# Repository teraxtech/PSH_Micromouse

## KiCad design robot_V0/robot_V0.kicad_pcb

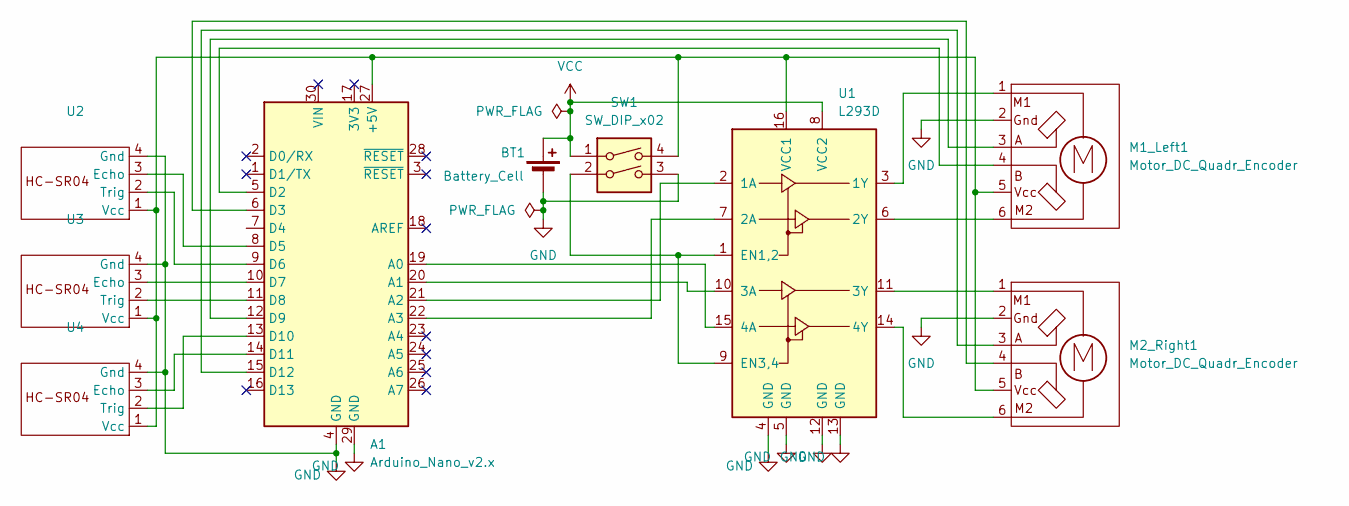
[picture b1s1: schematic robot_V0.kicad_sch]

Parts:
A1: Arduino_Nano_v2.x; Arduino_Nano
BT1: Battery_Cell; PinHeader_1x02_P2.54mm_Vertical
M1_Left1, M2_Right1: Motor_DC_Quadr_Encoder; Molex_CLIK-Mate_505405-0670_1x06-1MP_P1.50mm_Vertical
SW1: SW_DIP_x02; SW_DIP_SPSTx02_Piano_10.8x6.64mm_W7.62mm_P2.54mm
U1: L293D; DIP-16_W7.62mm
U2, U3, U4: XCVR_HC-SR04

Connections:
GND: A1.4 (GND), A1.29 (GND), BT1.2 (-), M1_Left1.2, M2_Right1.2, SW1.3, U1.4 (GND), U1.5 (GND), U1.12 (GND), U1.13 (GND), U2.4 (Gnd), U3.4 (Gnd), U4.4 (Gnd)
unnamed: A1.27 (+5V), M1_Left1.5, M2_Right1.5, SW1.4, U1.16 (VCC1), U2.1 (Vcc), U3.1 (Vcc), U4.1 (Vcc)
unnamed: A1.19 (A0), U1.15 (4A)
unnamed: A1.20 (A1), U1.10 (3A)
unnamed: A1.21 (A2), U1.2 (1A)
unnamed: A1.22 (A3), U1.7 (2A)
unnamed: A1.5 (D2), M1_Left1.4
unnamed: A1.6 (D3), M2_Right1.4
unnamed: A1.8 (D5), U2.3 (Echo)
unnamed: A1.9 (D6), U2.2 (Trig)
unnamed: A1.10 (D7), U3.3 (Echo)
unnamed: A1.11 (D8), U3.2 (Trig)
unnamed: A1.12 (D9), M1_Left1.3
unnamed: A1.13 (D10), U4.2 (Trig)
unnamed: A1.14 (D11), U4.3 (Echo)
unnamed: A1.15 (D12), M2_Right1.3
unnamed: M1_Left1.1, U1.3 (1Y)
unnamed: M1_Left1.6, U1.6 (2Y)
unnamed: M2_Right1.1, U1.11 (3Y)
unnamed: M2_Right1.6, U1.14 (4Y)
unnamed: SW1.2, U1.1 (EN1,2), U1.9 (EN3,4)
VCC: BT1.1 (+), SW1.1, U1.8 (VCC2)

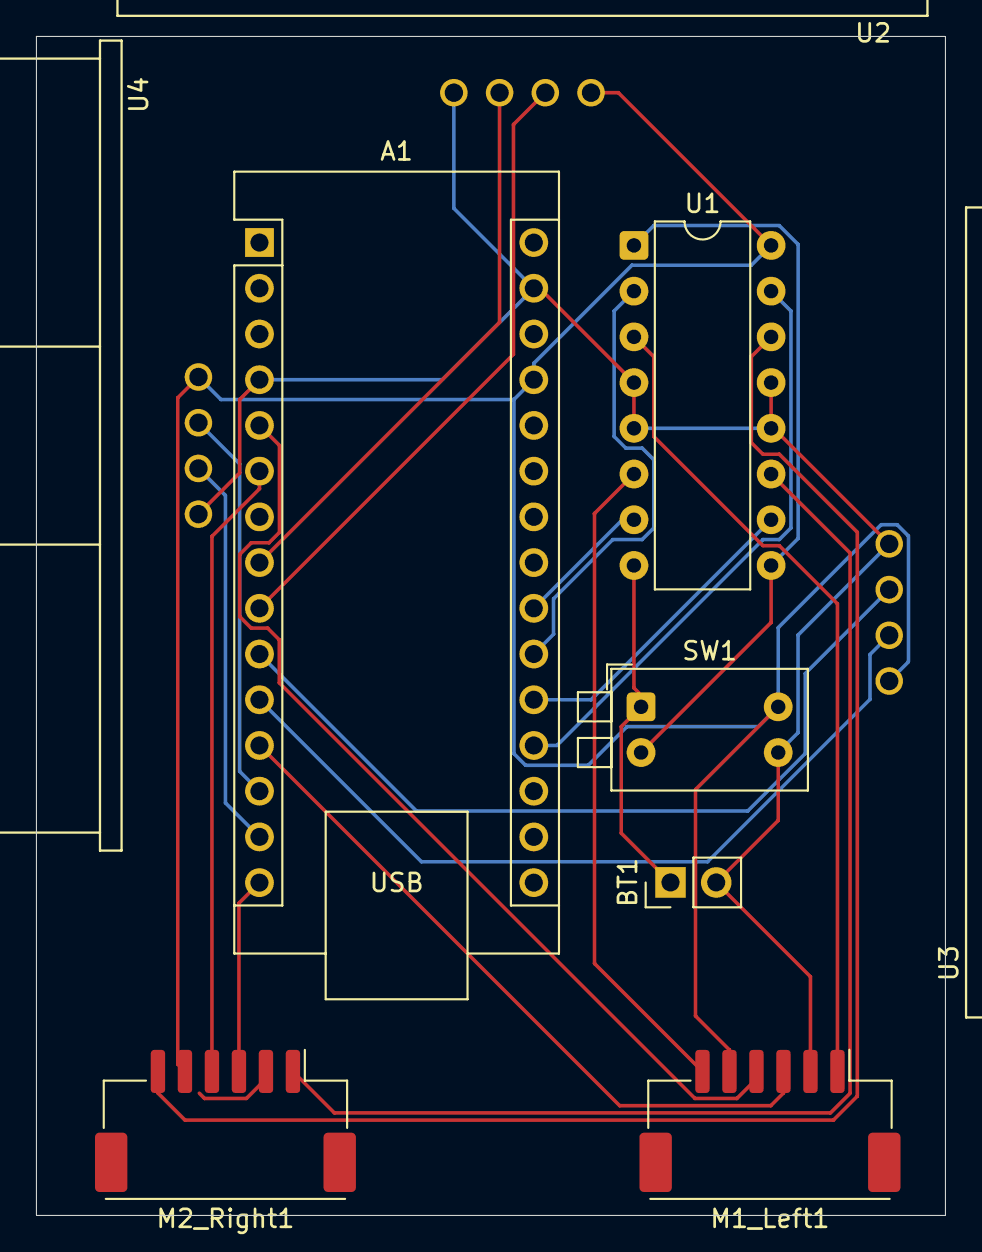
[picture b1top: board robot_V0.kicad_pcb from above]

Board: 2 copper layers, 50.5 x 65.5 mm, 9 parts (0 on the bottom side), 22 nets.

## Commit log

2026-02-09 Got encoders to work
2026-02-20 Implemented motor control as a class
2026-02-21 Create dist_sensors.ino
    HC-SR04 Ultrasonic Rangefinder
    Distance sensors Left & Right
2026-03-19 Robot can roll around and use ultrasonic sensors
2026-03-19 Made a pcb for the current robot
2026-03-21 Motors run inconsistently
2026-03-21 Updated .gitignore
2026-03-21 Added micromouse_floodfill_final.ino
